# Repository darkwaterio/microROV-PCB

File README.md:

# microROV PCB files

The pcb directory has directories containing the Eagle PCB schematic and board files for the Mk1 and Mk2 versions of the controller and a zip file of the Gerber files you'll need to send to a manufacturer if you don't want to modify the deisgns. We've tried them with [Ragworm](http://ragworm.eu/) and [Oshpark](https://oshpark.com/).

If you want a ready made board, a board with all the parts you need or even a pre-soldered board then you can get them from our [shop](http://darkwater.io/shop/) and help fund future projects.

##Build instructions

Build instructions are online at Instructables.
http://www.instructables.com/id/Make-a-Lego-ROV-part-2-the-controller/

##License

This work is licensed under the Creative Commons Attribution-NonCommercial-ShareAlike 4.0 International License. To view a copy of this license, visit http://creativecommons.org/licenses/by-nc-sa/4.0/ or send a letter to Creative Commons, 444 Castro Street, Suite 900, Mountain View, California, 94041, USA.

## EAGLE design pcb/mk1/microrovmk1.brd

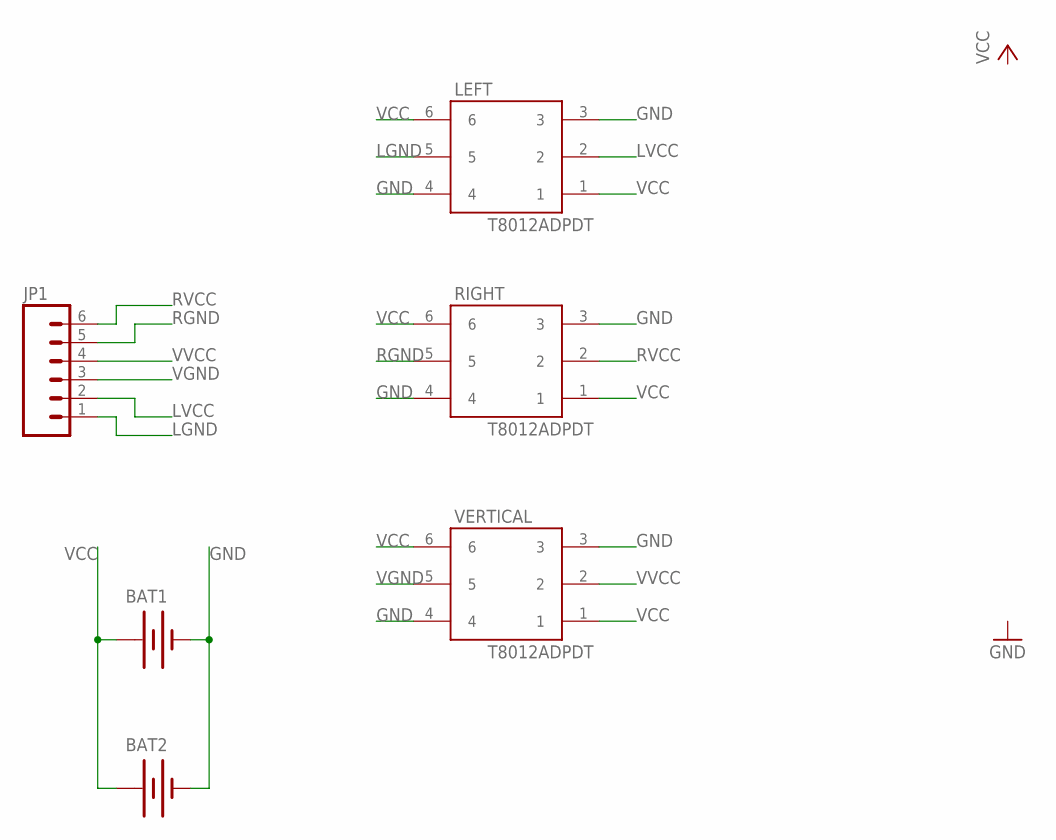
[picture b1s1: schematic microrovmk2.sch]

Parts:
BAT1, BAT2: BATTERY9V; BATTCON_9V
JP1: M06LOCK_LONGPADS; 1X06_LOCK_LONGPADS
LEFT: T8012ADPDT; T8012A
RIGHT: T8012ADPDT; T8012A
VERTICAL: T8012ADPDT; T8012A

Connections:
GND: BAT1.-, BAT2.-, LEFT.3, LEFT.4, RIGHT.3, RIGHT.4, VERTICAL.3, VERTICAL.4
LGND: JP1.1, LEFT.5
LVCC: JP1.2, LEFT.2
RGND: JP1.5, RIGHT.5
RVCC: JP1.6, RIGHT.2
VCC: BAT1.+, BAT2.+, LEFT.1, LEFT.6, RIGHT.1, RIGHT.6, VERTICAL.1, VERTICAL.6
VGND: JP1.3, VERTICAL.5
VVCC: JP1.4, VERTICAL.2

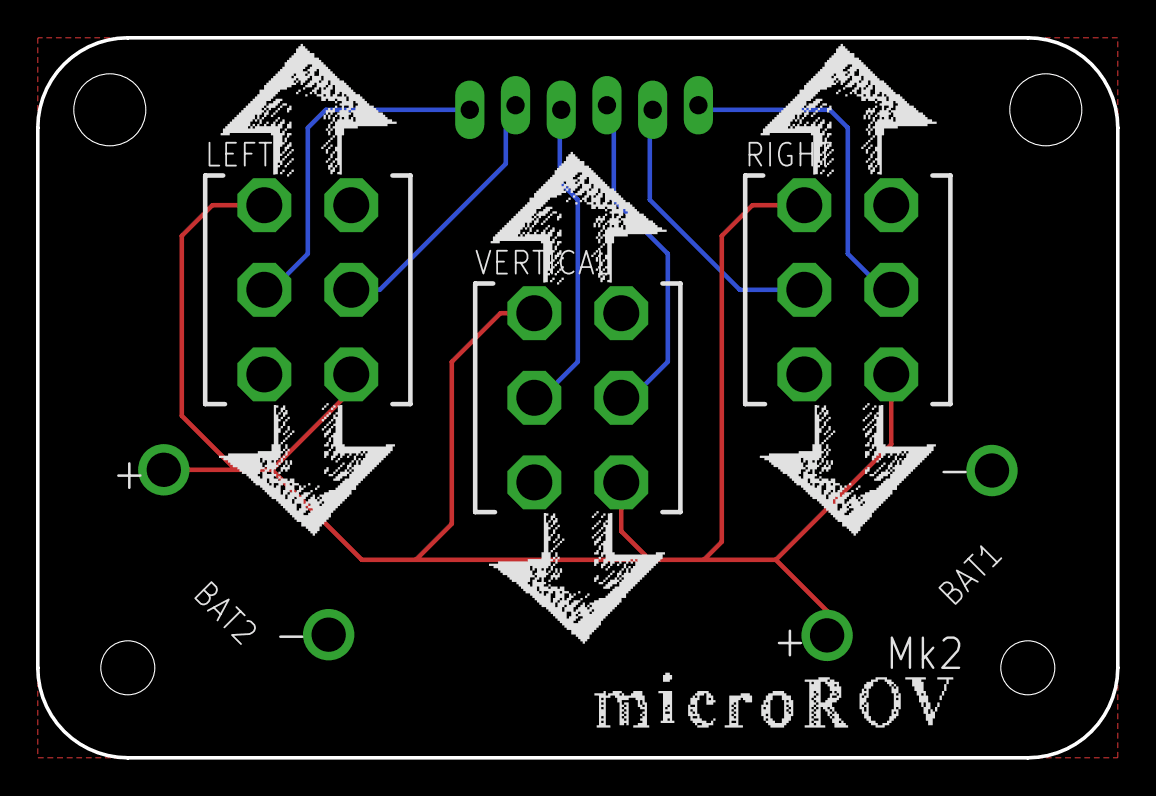
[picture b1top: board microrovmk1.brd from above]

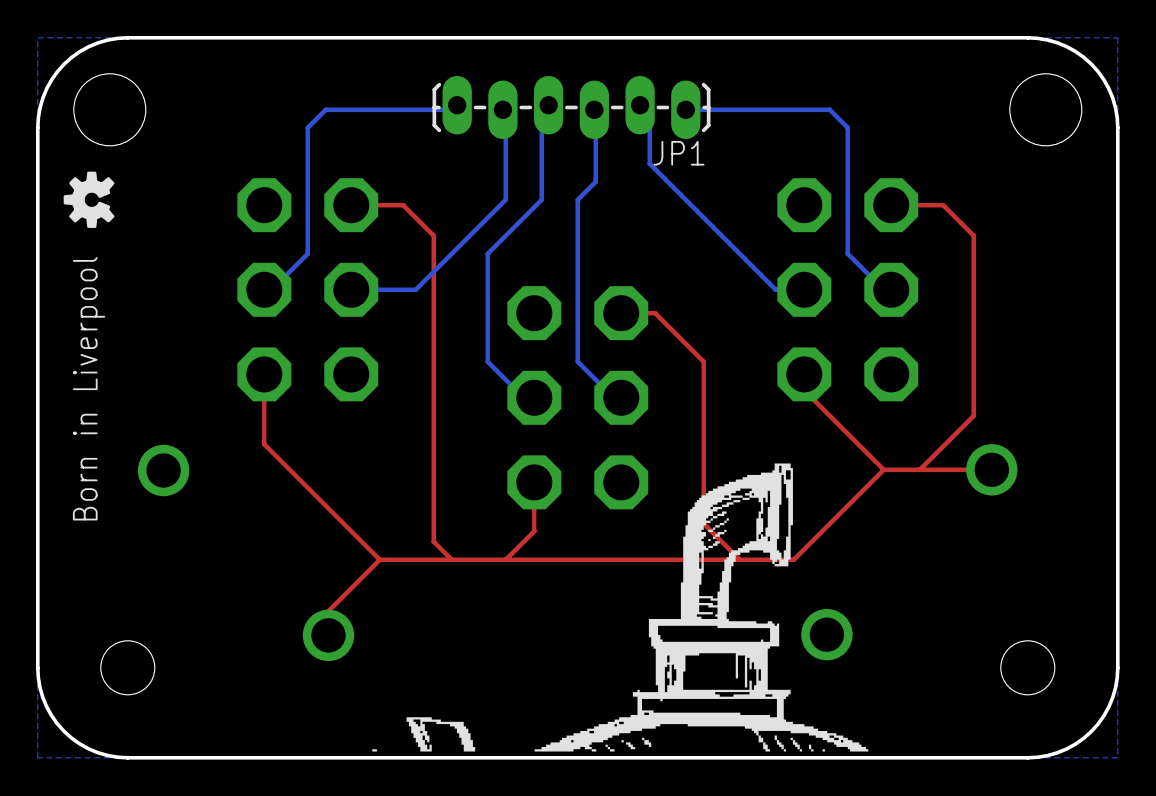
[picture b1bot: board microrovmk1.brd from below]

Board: 2 copper layers, 60.0 x 40.0 mm, 15 parts (3 on the bottom side), 8 nets.

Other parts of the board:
U$1: OSHW-LOGO-S
U$2, U$3, U$4, U$5, U$7, U$9: RIGHTARROW
U$6: MICROROV
U$8: SUBTOP

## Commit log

2015-06-03 Initial PCB designs
2015-07-01 insutrcutions
2015-07-01 correct link

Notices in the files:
parts and their libraries:
SparkFun-Connectors: Licensing: Creative Commons ShareAlike 4.0 International - https://creativecommons.org/licenses/by-sa/4.0
